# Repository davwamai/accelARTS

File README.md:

# accelARTS
Introductory project for the Adaptive Real-Time Systems laboratory. Circuit that captures and saves accelerometer data to a Micro-SD card via Arduino interface.

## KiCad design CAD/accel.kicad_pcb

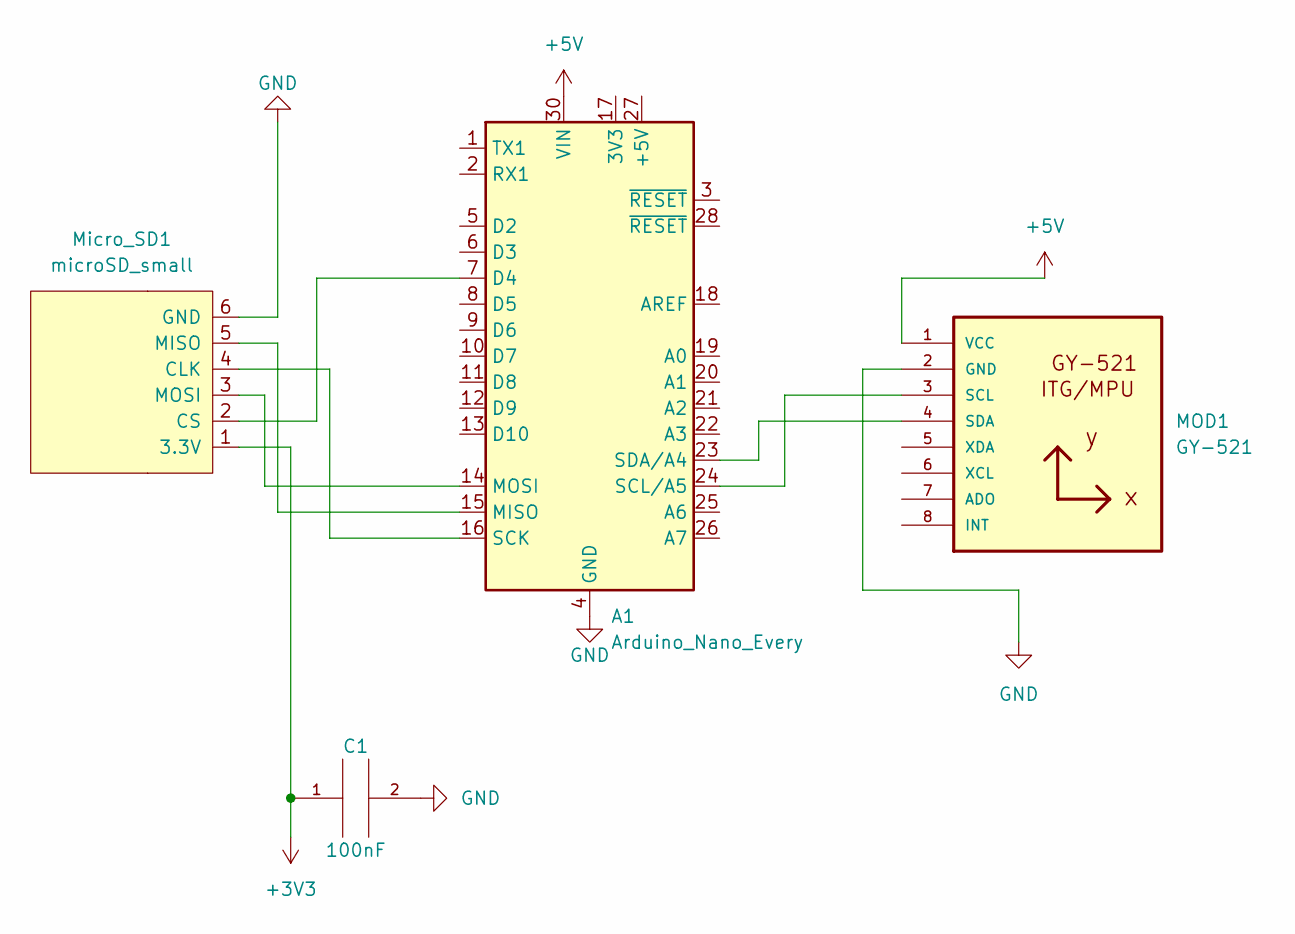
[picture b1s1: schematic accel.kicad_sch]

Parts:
A1: Arduino_Nano_Every; Arduino_Nano
C1: 100nF; CP_Elec_3x5.4
MOD1: GY-521
Micro_SD1: microSD_small; small_microSD_v2

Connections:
+3V3: C1.1, Micro_SD1.1 (3.3V)
+5V: A1.30 (VIN), MOD1.1 (VCC)
GND: A1.4 (GND), A1.29 (GND), C1.2, MOD1.2 (GND), Micro_SD1.6 (GND)
unnamed: A1.7 (D4), Micro_SD1.2 (CS)
unnamed: A1.14 (MOSI), Micro_SD1.3 (MOSI)
unnamed: A1.15 (MISO), Micro_SD1.5 (MISO)
unnamed: A1.16 (SCK), Micro_SD1.4 (CLK)
unnamed: A1.23 (SDA/A4), MOD1.4 (SDA)
unnamed: A1.24 (SCL/A5), MOD1.3 (SCL)

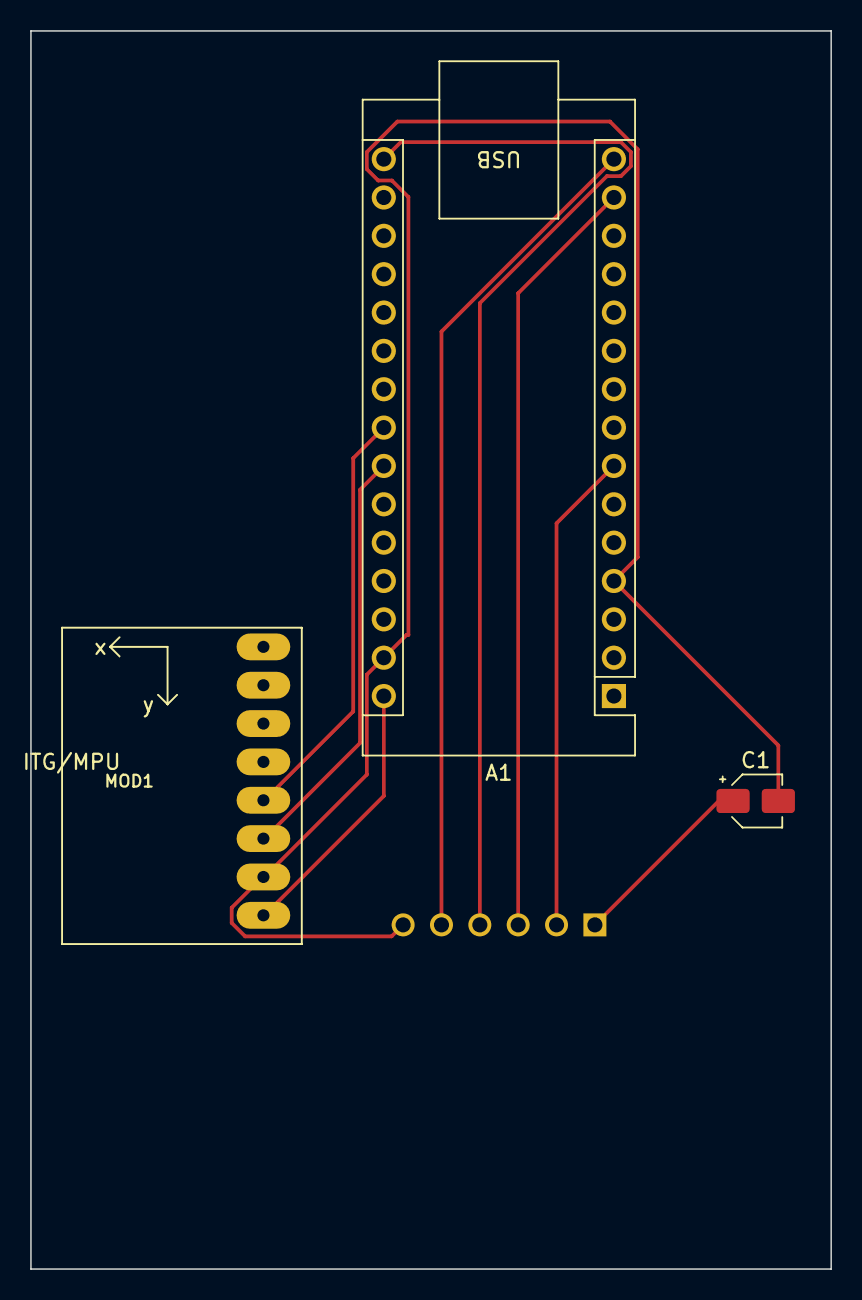
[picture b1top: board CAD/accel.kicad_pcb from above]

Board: 2 copper layers, 53.0 x 82.0 mm, 4 parts (0 on the bottom side), 9 nets.

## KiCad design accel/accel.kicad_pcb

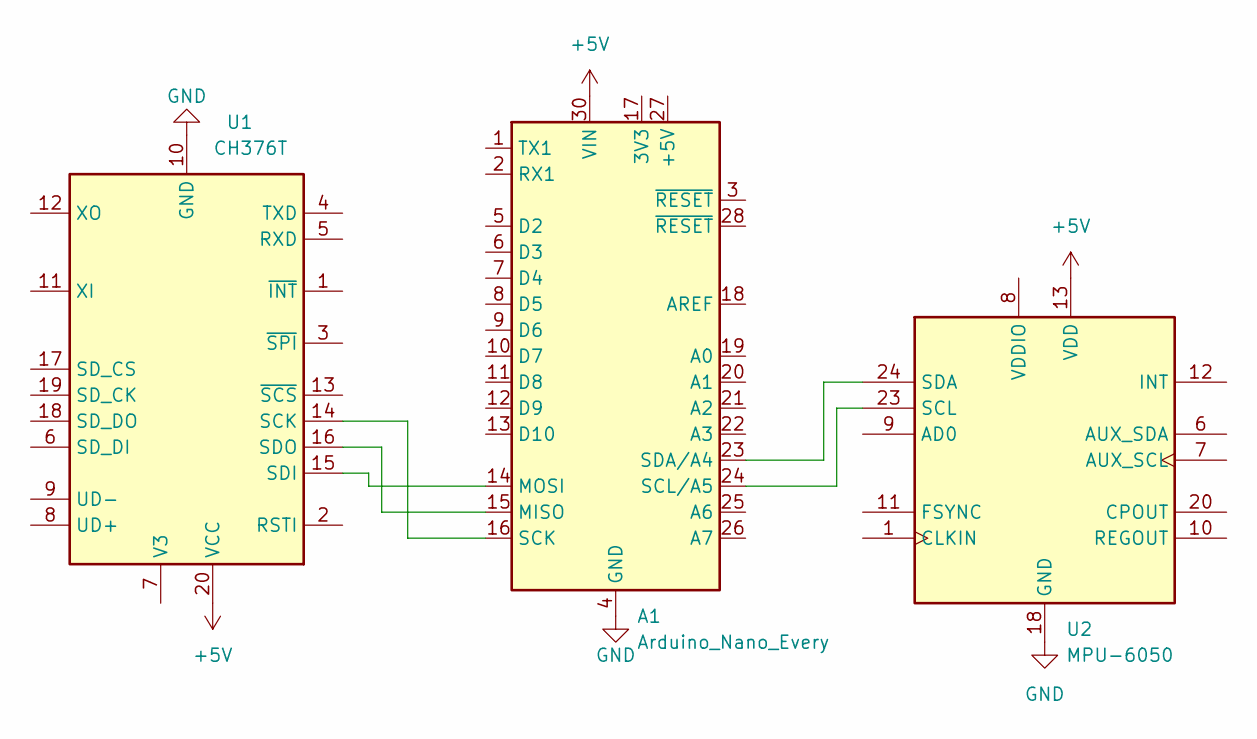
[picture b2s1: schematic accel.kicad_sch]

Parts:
A1: Arduino_Nano_Every; Arduino_Nano
U1: CH376T; SSOP-20_5.3x7.2mm_P0.65mm
U2: MPU-6050; InvenSense_QFN-24_4x4mm_P0.5mm

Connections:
+5V: A1.30 (VIN), U1.20 (VCC), U2.13 (VDD)
GND: A1.4 (GND), A1.29 (GND), U1.10 (GND), U2.18 (GND)
unnamed: A1.14 (MOSI), U1.15 (SDI)
unnamed: A1.15 (MISO), U1.16 (SDO)
unnamed: A1.16 (SCK), U1.14 (SCK)
unnamed: A1.23 (SDA/A4), U2.24 (SDA)
unnamed: A1.24 (SCL/A5), U2.23 (SCL)

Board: 2 copper layers, 3 parts (0 on the bottom side), 7 nets, no tracks yet.

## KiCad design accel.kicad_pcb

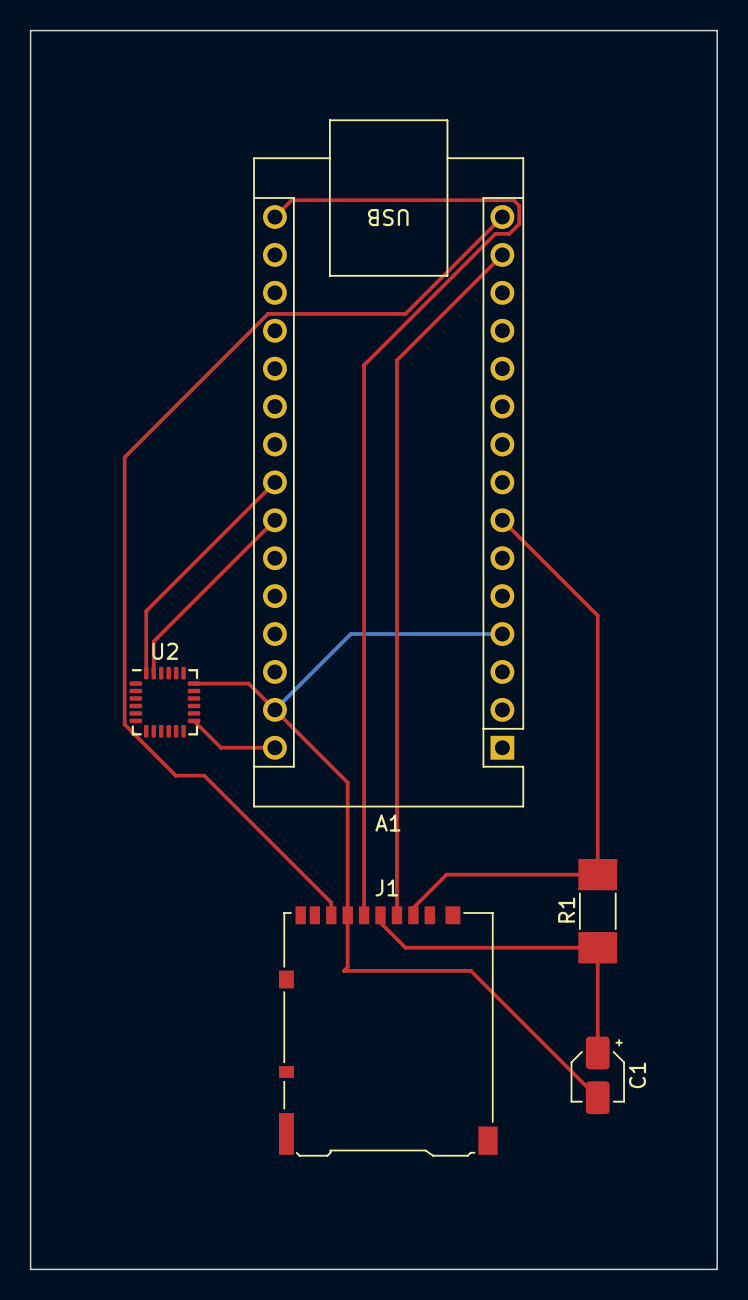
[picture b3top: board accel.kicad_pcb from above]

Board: 2 copper layers, 46.0 x 83.0 mm, 5 parts (0 on the bottom side), 9 nets.

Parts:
A1: Arduino_Nano_Every; Arduino_Nano
C1: 100nF; CP_Elec_3x5.4
J1: Micro_SD_Card; microSD_HC_Hirose_DM3AT-SF-PEJM5
R1: 1K; R_MELF_MMB-0207
U2: MPU-6050; InvenSense_QFN-24_4x4mm_P0.5mm

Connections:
+3V3: C1.1, J1.4 (VDD), R1.1
+5V: A1.30 (VIN), U2.13 (VDD)
GND: A1.4 (GND), A1.29 (GND), C1.2, J1.6 (VSS), U2.18 (GND)
unnamed: A1.7 (D4), J1.2 (DAT3/CD), R1.2
unnamed: A1.14 (MOSI), J1.3 (CMD)
unnamed: A1.15 (MISO), J1.7 (DAT0)
unnamed: A1.16 (SCK), J1.5 (CLK)
unnamed: A1.23 (SDA/A4), U2.24 (SDA)
unnamed: A1.24 (SCL/A5), U2.23 (SCL)

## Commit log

2023-01-17 initial
2023-01-17 found chip select
2023-01-19 final .ino and cad updates
2023-01-20 finalization
